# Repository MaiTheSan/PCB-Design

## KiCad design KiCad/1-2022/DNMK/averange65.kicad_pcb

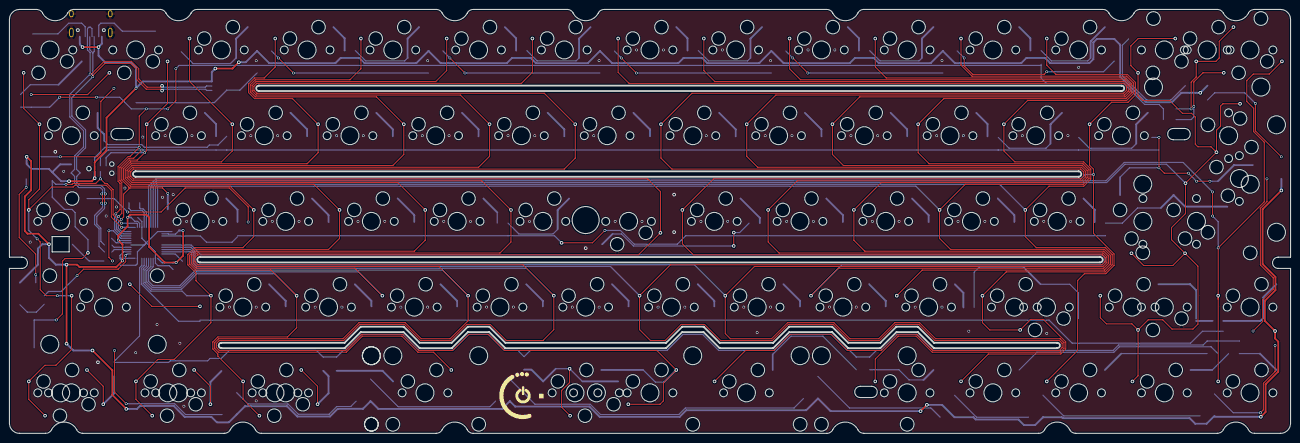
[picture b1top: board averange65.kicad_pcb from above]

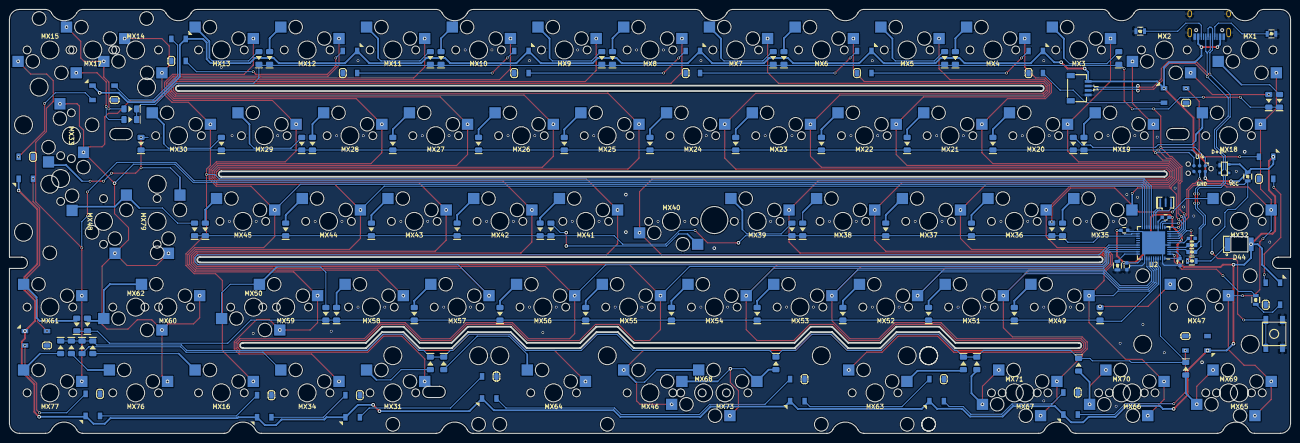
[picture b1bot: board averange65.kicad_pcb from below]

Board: 2 copper layers, 284.7 x 94.2 mm, 183 parts (107 on the bottom side), 122 nets.

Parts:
C1: 10uF; C_0603
C4, C5, C7: 0.1uF; C_0603
C6: 1uF; C_0603
D1, D2, D3, D4, D5, D6, D7, D8, D9, D10, D11, D12, D13, D14, D15, D16, D17, D18, D19, D20, D21, D22, D23, D24, D25, D26, D27, D28, D29, D30, D31, D33, D34, D35, D36, D37, D38, D39, D40, D41, D42, D43, D45, D46, D48, D49, D50, D51, D52, D53, D54, D55, D56, D57, D58, D59, D61, D62, D63, D64, D65, D66, D70, D71, D72, D73: D; DIODE_1206_SawnsProjects
D44: LED; LED-6028
J1: Conn_01x04_Female; JST-SR-4
MX1, MX2, MX3, MX4, MX5, MX6, MX7, MX8, MX9, MX10, MX11, MX12, MX13, MX14, MX15, MX16, MX19, MX20, MX21, MX22, MX23, MX24, MX25, MX26, MX27, MX28, MX29, MX30, MX31, MX34, MX35, MX36, MX37, MX38, MX39, MX40, MX41, MX42, MX43, MX44, MX45, MX49, MX51, MX52, MX53, MX54, MX55, MX56, MX57, MX58, MX59, MX61, MX62, MX70, MX76, MX77, MX79: 1U; MXOnly-1U-Hotswap
MX17: 2U; MXOnly-2U-Hotswap
MX18, MX33, MX69, MX71: 1.5U; MXOnly-1.5U-Hotswap
MX32: 1.75U; MXOnly-1.25U-Hotswap
MX46: 7U; MXOnly-7U-Hotswap-ReversedStabilizers
MX47: 2.25U; MXOnly-2.25U-Hotswap
MX48: 2.25U; MXOnly-2.25U-Hotswap-ReversedStabilizers-L
MX50, MX60: 1.75U; MXOnly-1.75U-Hotswap
MX63: 2.25U; MXOnly-2.25U-Hotswap-ReversedStabilizers
MX64: 2.75U; MXOnly-2.75U-Hotswap-ReversedStabilizers
MX65, MX66, MX67, MX73: 1.25U; MXOnly-1.25U-Hotswap
MX68: 6.25U; MXOnly-6.25U-Hotswap
MX78: ISO; MXOnly-ISO-ROTATED-Hotswap-R
R1, R2: 5.1k; R_0805
R3, R4: 22; R_0603
R5: 10k; R_0805
R6: 1k; R_0805
R7, R8: 300R; R_0805
RGB1, RGB2, RGB3, RGB4, RGB5, RGB6, RGB7, RGB8, RGB9, RGB10, RGB11, RGB12, RGB13, RGB14, RGB15, RGB16, RGB17, RGB18, RGB19, RGB20: WS2812B; LED_WS2812B_PLCC4_5.0x5.0mm_P3.2mm
SW1: SW_Push; SKQG-1155865
U1: PRTR5V0U2X; SOT143B
U2: ATmega32U4-MU; QFN-44-1EP_7x7mm_P0.5mm_EP5.15x5.15mm
U4: STF202-22T1G; Tag-Connect_TC2030-IDC-NL_2x03_P1.27mm_Vertical
USB1: HRO-TYPE-C-31-M-12; HRO-TYPE-C-31-M-12-Assembly
Y1: Crystal_GND2; Resonator_SMD_muRata_CSTxExxV-3Pin_3.0x1.1mm

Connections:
+5V: C1.2, C4.2, C5.2, C7.2, D44.2, J1.1, R5.1, RGB1.1, RGB2.1, RGB3.1, RGB4.1, RGB5.1, RGB6.1, RGB7.1, RGB8.1, RGB9.1, RGB10.1, RGB11.1, RGB12.1, RGB13.1, RGB14.1, RGB15.1, RGB16.1, RGB17.1, RGB18.1, RGB19.1, RGB20.1, U1.4, U2.2, U2.7, U2.14, U2.24, U2.34, U2.44, U4.2, USB1.2, USB1.11
A+: J1.3, R4.2, U1.2, USB1.6, USB1.8
A-: J1.2, R3.2, U1.3, USB1.5, USB1.7
CapLK: R8.2, U2.8
Col0: MX1.2, MX18.1, MX32.1, MX47.1, MX65.1, MX69.2, U2.12
Col1: MX2.1, MX19.1, MX35.1, U2.11, U4.5
Col2: MX3.1, MX20.1, MX36.1, MX49.1, MX66.1, MX70.2, U2.39
Col3: MX4.1, MX21.1, MX37.1, MX51.1, MX67.1, MX71.2, U2.38
Col4: MX5.1, MX22.1, MX38.1, MX52.1, U2.37
Col5: MX6.1, MX23.1, MX39.1, MX53.1, MX63.2, U2.36
Col6: MX7.1, MX24.1, MX40.1, MX46.2, MX54.1, MX68.1, MX73.2, U2.32
Col7: MX8.1, MX25.1, MX41.1, MX55.1, MX64.1, U2.31
Col8: MX9.1, MX26.1, MX31.1, MX42.1, MX56.1, U2.30
Col9: MX10.1, MX27.1, MX43.1, MX57.1, U2.29
Col10: MX11.1, MX28.1, MX44.1, MX58.1, U2.22
Col11: MX12.1, MX29.1, MX34.1, MX45.1, MX50.2, MX59.1, U2.21
Col12: MX13.1, MX16.1, MX30.1, U2.18
Col13: MX14.2, MX17.1, MX33.1, MX48.1, MX60.1, MX62.2, MX76.1, MX78.2, MX79.1, U2.20
Col14: MX15.1, MX61.1, MX77.1, U2.19
D+: R4.1, U2.4
D-: R3.1, U2.3
GND: C1.1, C4.1, C5.1, C6.2, C7.1, J1.4, R1.1, R2.1, R6.1, RGB1.3, RGB2.3, RGB3.3, RGB4.3, RGB5.3, RGB6.3, RGB7.3, RGB8.3, RGB9.3, RGB10.3, RGB11.3, RGB12.3, RGB13.3, RGB14.3, RGB15.3, RGB16.3, RGB17.3, RGB18.3, RGB19.3, RGB20.3, SW1.1, U1.1, U2.5, U2.15, U2.23, U2.35, U2.43, U2.45, U4.6, USB1.1, USB1.12, USB1.13, Y1.2
MOSI: D17.1, D18.1, D19.1, D20.1, D21.1, D22.1, D23.1, D24.1, D25.1, D26.1, D27.1, D28.1, D29.1, D31.1, U2.10, U4.3
unnamed: C6.1, U2.6
unnamed: D1.2, MX1.1
unnamed: D2.2, MX2.2
unnamed: D3.2, MX3.2
unnamed: D4.2, MX4.2
unnamed: D5.2, MX5.2
unnamed: D6.2, MX6.2
unnamed: D7.2, MX7.2
unnamed: D8.2, MX8.2
unnamed: D9.2, MX9.2
unnamed: D10.2, MX10.2
unnamed: D11.2, MX11.2
unnamed: D12.2, MX12.2
unnamed: D13.2, MX13.2
unnamed: D14.2, MX14.1, MX17.2
unnamed: D15.2, MX15.2
unnamed: D16.2, MX16.2
unnamed: D17.2, MX18.2
unnamed: D18.2, MX19.2
unnamed: D19.2, MX20.2
unnamed: D20.2, MX21.2
unnamed: D21.2, MX22.2
unnamed: D22.2, MX23.2
unnamed: D23.2, MX24.2
unnamed: D24.2, MX25.2
unnamed: D25.2, MX26.2
unnamed: D26.2, MX27.2
unnamed: D27.2, MX28.2
unnamed: D28.2, MX29.2
unnamed: D29.2, MX30.2
unnamed: D30.2, MX32.2
unnamed: D31.2, MX33.2, MX79.2
unnamed: D33.2, MX35.2
unnamed: D34.2, MX36.2
unnamed: D35.2, MX37.2
unnamed: D36.2, MX38.2
unnamed: D37.2, MX39.2
unnamed: D38.2, MX40.2
unnamed: D39.2, MX41.2
unnamed: D40.2, MX42.2
unnamed: D41.2, MX43.2
unnamed: D42.2, MX44.2
unnamed: D43.2, MX45.2
unnamed: D44.1, R8.1
unnamed: D45.2, MX48.2, MX78.1
unnamed: D46.2, MX47.2
unnamed: D48.2, MX49.2
unnamed: D49.2, MX51.2
unnamed: D50.2, MX52.2
unnamed: D51.2, MX53.2
unnamed: D52.2, MX54.2
unnamed: D53.2, MX55.2
unnamed: D54.2, MX56.2
unnamed: D55.2, MX57.2
unnamed: D56.2, MX58.2
unnamed: D57.2, MX50.1, MX59.2
unnamed: D58.2, MX60.2, MX62.1
unnamed: D59.2, MX61.2
unnamed: D61.2, MX65.2, MX69.1
unnamed: D62.2, MX66.2, MX70.1
unnamed: D63.2, MX67.2, MX71.1
unnamed: D64.2, MX63.1
unnamed: D65.2, MX46.1, MX68.2, MX73.1
unnamed: D66.2, MX64.2
unnamed: D70.2, MX31.2
unnamed: D71.2, MX34.2
unnamed: D72.2, MX76.2
unnamed: D73.2, MX77.2
unnamed: R1.2, USB1.4
unnamed: R2.2, USB1.10
unnamed: R6.2, U2.33
unnamed: R7.2, U2.1
unnamed: RGB1.2, RGB2.4
unnamed: RGB1.4, RGB11.2
unnamed: RGB2.2, RGB3.4
unnamed: RGB3.2, RGB4.4
unnamed: RGB4.2, RGB5.4
unnamed: RGB5.2, RGB6.4
unnamed: RGB6.2, RGB7.4
unnamed: RGB7.2, RGB8.4
unnamed: RGB8.2, RGB9.4
unnamed: RGB10.2, RGB20.4
unnamed: RGB9.2, RGB10.4
unnamed: RGB11.4, RGB12.2
unnamed: RGB13.4, RGB14.2
unnamed: RGB14.4, RGB15.2
unnamed: RGB15.4, RGB16.2
unnamed: RGB16.4, RGB17.2
unnamed: RGB17.4, RGB18.2
unnamed: RGB18.4, RGB19.2
unnamed: RGB19.4, RGB20.2
unnamed: U2.16, Y1.3
unnamed: U2.17, Y1.1
RGBLED: R7.1, RGB12.4
RST: R5.2, SW1.2, U2.13, U4.4
Row0: D1.1, D2.1, D3.1, D4.1, D5.1, D6.1, D7.1, D8.1, D9.1, D10.1, D11.1, D12.1, D13.1, D14.1, D15.1, U2.9, U4.1
Row2: D30.1, D33.1, D34.1, D35.1, D36.1, D37.1, D38.1, D39.1, D40.1, D41.1, D42.1, D43.1, D45.1, U2.25
Row3: D46.1, D48.1, D49.1, D50.1, D51.1, D52.1, D53.1, D54.1, D55.1, D56.1, D57.1, D58.1, D59.1, U2.40
Row4: D16.1, D61.1, D62.1, D63.1, D64.1, D65.1, D66.1, D70.1, D71.1, D72.1, D73.1, U2.41

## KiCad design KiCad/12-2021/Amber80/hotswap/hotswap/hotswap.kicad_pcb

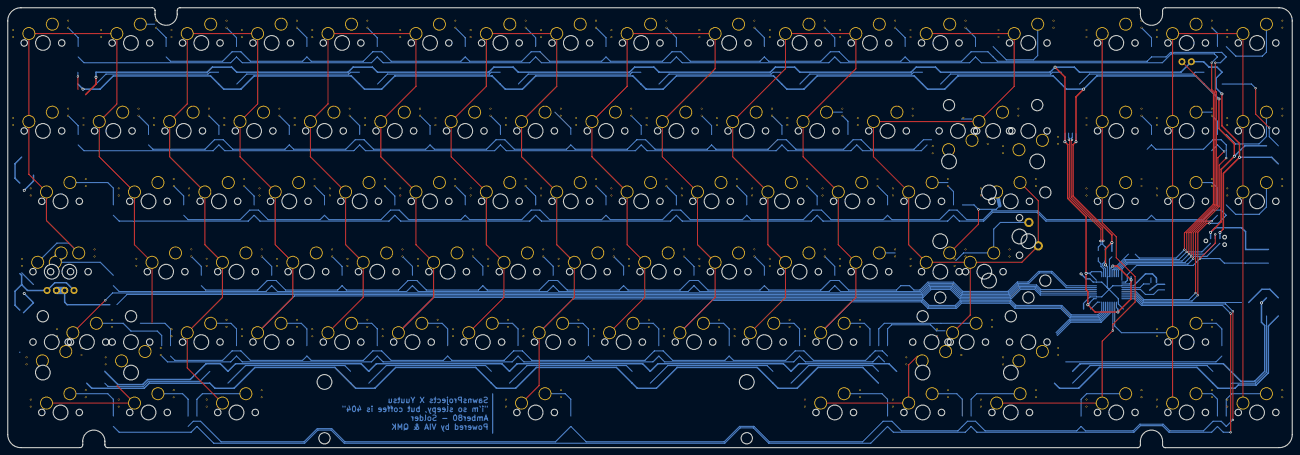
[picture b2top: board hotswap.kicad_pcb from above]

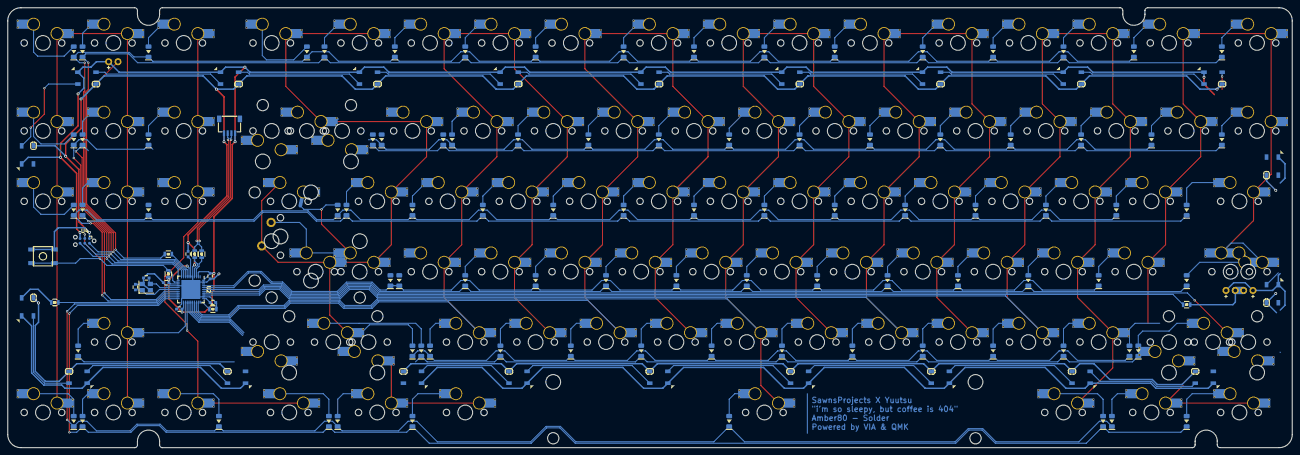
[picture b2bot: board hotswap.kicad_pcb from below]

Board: 2 copper layers, 347.7 x 119.1 mm, 230 parts (131 on the bottom side), 149 nets.

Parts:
C1: 10uF; C_0603
C2, C3: 22pF; C_0603
C4, C5, C7: 0.1uF; C_0603
C6: 1uF; C_0603
D1, D2, D3, D4, D5, D6, D7, D8, D9, D10, D11, D12, D13, D14, D15, D16, D17, D18, D19, D20, D21, D22, D23, D25, D26, D27, D28, D29, D31, D32, D33, D34, D35, D37, D38, D39, D40, D41, D43, D44, D45, D46, D47, D48, D49, D50, D51, D52, D53, D55, D56, D57, D58, D59, D61, D62, D63, D64, D65, D67, D68, D69, D70, D71, D73, D74, D75, D77, D78, D79, D80, D81, D82, D83, D84, D86, D87, D90, D91, D92, D93, D96, D97, D98, D101, D102, D103, D104, D105, D108: D; DIODE_1206_SawnsProjects
D24, D30, D36, D42, D54, D60, D66, D72, D76, D85, D88, D89, D94, D95, D99, D100, D106, D107, D109, D110, D111, D112: WS2812B; LED_WS2812B_PLCC4_5.0x5.0mm_P3.2mm
D113, D115: LED; MXOnly-LEDONLY-FLIPPED
D114: LED; MXOnly-LEDONLY
J1: Conn_01x04_Female; JST-SR-4
MX1, MX2, MX3, MX4, MX5, MX6, MX7, MX8, MX9, MX10, MX11, MX12, MX13, MX14, MX16, MX17, MX22, MX23, MX24, MX25, MX26, MX27, MX28, MX29, MX30, MX32, MX33, MX34, MX35, MX37, MX38, MX39, MX40, MX41, MX42, MX43, MX44, MX45, MX47, MX48, MX49, MX50, MX52, MX53, MX54, MX55, MX57, MX58, MX59, MX60, MX62, MX63, MX64, MX65, MX67, MX68, MX69, MX70, MX72, MX73, MX74, MX75, MX77, MX78, MX79, MX82, MX85, MX87, MX88, MX92, MX93, MX96, MX97, MX98, MX101, MX102, MX103, MX104, MX105, MX108: 1U; MXOnly-1U-Hotswap-Sawns
MX15, MX18, MX21, MX31, MX36, MX46: 1.5U; MXOnly-1.5U-Hotswap-Sawns
MX19, MX80: 1.75U; MXOnly-1.75U-Hotswap-Sawns
MX20, MX71: 1.25U; MXOnly-1.25U-Hotswap-Sawns
MX51: 2U; MXOnly-2U-Hotswap-Sawns
MX56: 7U; MXOnly-7U-Hotswap-ReversedStabilizers-Sawns
MX61: 2.75U; MXOnly-2.75U-Hotswap-Sawns
MX66: 2.25U; MXOnly-2.25U-Hotswap-Sawns
MX76: ISO; MXOnly-ISO-ROTATED-ReversedStabilizers-NoLED
MX84: 2.25U; MXOnly-2.75U-Hotswap-ReversedStabilizers-Sawns
R3, R4: 22; R_0805
R5: 10k; R_0805
R6: 1k; R_0805
R7, R8, R9: 300R; R_0805
SW1: SW_Push; SKQG-1155865-fix
U2: ATmega32U4-MU; QFN-44-1EP_7x7mm_P0.5mm_EP5.15x5.15mm
U4: STF202-22T1G; Tag-Connect_TC2030-IDC-NL_2x03_P1.27mm_Vertical
Y1: 16Mhz; Crystal_SMD_3225-4Pin_3.2x2.5mm

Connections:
+5V: C1.2, C4.2, C5.2, C7.2, D24.1, D30.1, D36.1, D42.1, D54.1, D60.1, D66.1, D72.1, D76.1, D85.1, D88.1, D89.1, D94.1, D95.1, D99.1, D100.1, D106.1, D107.1, D109.1, D110.1, D111.1, D112.1, D113.2, D114.2, D115.2, J1.1, R5.1, U2.2, U2.7, U2.14, U2.24, U2.34, U2.44, U4.5
C0: MX1.1, MX2.1, MX17.1, MX18.1, MX19.2, MX20.1, MX21.1, MX22.1, MX23.1, MX24.1, MX25.1, MX26.1, MX66.1, MX71.1, U2.39
C1: MX3.1, MX4.1, MX27.1, MX28.1, MX29.1, MX30.1, MX31.1, MX32.1, MX33.1, MX34.1, MX35.1, U2.37
C2: MX5.1, MX6.1, MX37.1, MX38.1, MX39.1, MX40.1, MX42.1, MX43.1, MX44.1, MX45.1, U2.36
C3: MX7.1, MX8.1, MX47.1, MX48.1, MX49.1, MX50.1, MX52.1, MX53.1, MX54.1, MX55.1, MX56.1, U2.32
C4: MX9.1, MX10.1, MX57.1, MX58.1, MX59.1, MX60.1, MX62.1, MX63.1, MX64.1, MX65.1, U2.31
C5: MX11.1, MX12.1, MX67.1, MX68.1, MX69.1, MX70.1, MX72.1, MX73.1, MX74.1, MX75.1, U2.30
C6: MX13.1, MX14.1, MX15.2, MX36.1, MX41.1, MX51.1, MX61.1, MX76.2, MX77.1, MX78.1, MX79.1, MX80.1, MX82.1, MX84.1, MX85.1, U2.29
C7: MX16.1, MX46.1, MX87.1, MX88.1, MX92.1, MX96.1, U2.26
C8: MX93.1, MX97.1, MX98.1, MX101.1, MX102.1, MX103.1, MX104.1, MX105.1, MX108.1, U2.25
D+: R3.1, U2.4
D-: R4.1, U2.3
DG+: J1.3, R3.2
DG-: J1.2, R4.2
GND: C1.1, C2.2, C3.2, C4.1, C5.1, C6.2, C7.1, D24.3, D30.3, D36.3, D42.3, D54.3, D60.3, D66.3, D72.3, D76.3, D85.3, D88.3, D89.3, D94.3, D95.3, D99.3, D100.3, D106.3, D107.3, D109.3, D110.3, D111.3, D112.3, J1.4, R6.1, SW1.1, U2.5, U2.15, U2.23, U2.35, U2.43, U2.45, U4.1, Y1.2, Y1.4
MISO: D2.1, D14.1, D26.1, D38.1, D50.1, D62.1, D74.1, D86.1, D98.1, U2.11, U4.6
MOSI: D7.1, D19.1, D31.1, D43.1, D55.1, D67.1, D79.1, D91.1, D103.1, U2.10, U4.4
unnamed: C2.1, U2.17, Y1.1
unnamed: C3.1, U2.16, Y1.3
unnamed: C6.1, U2.6
unnamed: D1.2, MX1.2
unnamed: D2.2, MX17.2
unnamed: D3.2, MX18.2
unnamed: D4.2, MX19.1, MX71.2
unnamed: D5.2, MX20.2, MX66.2
unnamed: D6.2, MX21.2
unnamed: D7.2, MX2.2
unnamed: D8.2, MX22.2
unnamed: D9.2, MX23.2
unnamed: D10.2, MX24.2
unnamed: D11.2, MX25.2
unnamed: D12.2, MX26.2
unnamed: D13.2, MX3.2
unnamed: D14.2, MX27.2
unnamed: D15.2, MX28.2
unnamed: D16.2, MX29.2
unnamed: D17.2, MX30.2
unnamed: D18.2, MX31.2
unnamed: D19.2, MX4.2
unnamed: D20.2, MX32.2
unnamed: D21.2, MX33.2
unnamed: D22.2, MX34.2
unnamed: D23.2, MX35.2
unnamed: D24.4, D30.2
unnamed: D25.2, MX5.2
unnamed: D26.2, MX37.2
unnamed: D27.2, MX38.2
unnamed: D28.2, MX39.2
unnamed: D29.2, MX40.2
unnamed: D30.4, D36.2
unnamed: D31.2, MX6.2
unnamed: D32.2, MX42.2
unnamed: D33.2, MX43.2
unnamed: D34.2, MX44.2
unnamed: D35.2, MX45.2
unnamed: D36.4, D42.2
unnamed: D37.2, MX7.2
unnamed: D38.2, MX47.2
unnamed: D39.2, MX48.2
unnamed: D40.2, MX49.2
unnamed: D41.2, MX50.2
unnamed: D42.4, D54.2
unnamed: D43.2, MX8.2
unnamed: D44.2, MX52.2
unnamed: D45.2, MX53.2
unnamed: D46.2, MX54.2
unnamed: D47.2, MX55.2
unnamed: D48.2, MX56.2
unnamed: D49.2, MX9.2
unnamed: D50.2, MX57.2
unnamed: D51.2, MX58.2
unnamed: D52.2, MX59.2
unnamed: D53.2, MX60.2
unnamed: D54.4, D60.2
unnamed: D55.2, MX10.2
unnamed: D56.2, MX62.2
unnamed: D57.2, MX63.2
unnamed: D58.2, MX64.2
unnamed: D59.2, MX65.2
unnamed: D60.4, D66.2
unnamed: D61.2, MX11.2
unnamed: D62.2, MX67.2
unnamed: D63.2, MX68.2
unnamed: D64.2, MX69.2
unnamed: D65.2, MX70.2
unnamed: D66.4, D72.2
unnamed: D67.2, MX12.2
unnamed: D68.2, MX72.2
unnamed: D69.2, MX73.2
unnamed: D70.2, MX74.2
unnamed: D71.2, MX75.2
unnamed: D72.4, D76.2
unnamed: D73.2, MX13.2
unnamed: D74.2, MX77.2
unnamed: D75.2, MX78.2
unnamed: D76.4, D85.2
unnamed: D77.2, MX61.2, MX80.2
unnamed: D78.2, MX36.2
unnamed: D79.2, MX14.2
unnamed: D80.2, MX51.2, MX82.2
unnamed: D81.2, MX15.1, MX79.2
unnamed: D82.2, MX76.1, MX84.2
unnamed: D83.2, MX85.2
unnamed: D84.2, MX41.2
unnamed: D85.4, D88.2
unnamed: D86.2, MX87.2
unnamed: D87.2, MX93.2
unnamed: D88.4, D89.2
unnamed: D89.4, D94.2
unnamed: D90.2, MX46.2
unnamed: D91.2, MX16.2
unnamed: D92.2, MX92.2
unnamed: D93.2, MX88.2
unnamed: D95.2, D99.4
unnamed: D95.4, R7.1
unnamed: D96.2, MX96.2
unnamed: D97.2, MX97.2
unnamed: D98.2, MX98.2
unnamed: D100.2, D106.4
unnamed: D99.2, D100.4
unnamed: D101.2, MX101.2
unnamed: D102.2, MX102.2
unnamed: D103.2, MX103.2
unnamed: D104.2, MX104.2
unnamed: D105.2, MX105.2
unnamed: D106.2, D107.4
unnamed: D107.2, D109.4
unnamed: D108.2, MX108.2
unnamed: D109.2, D110.4
unnamed: D110.2, D111.4
unnamed: D111.2, D112.4
unnamed: D94.4, D112.2
unnamed: D113.1, R8.1
unnamed: D114.1, D115.1, R9.1
unnamed: R6.2, U2.33
R0: D1.1, D13.1, D25.1, D37.1, D49.1, D61.1, D73.1, D97.1, U2.9, U4.2
R3: D8.1, D20.1, D32.1, D44.1, D56.1, D68.1, D80.1, D92.1, D104.1, U2.12
R4: D3.1, D15.1, D27.1, D39.1, D51.1, D63.1, D75.1, D87.1, U2.18
R5: D9.1, D21.1, D33.1, D45.1, D57.1, D69.1, D81.1, D93.1, D105.1, U2.19
R6: D4.1, D16.1, D28.1, D40.1, D52.1, D64.1, U2.40
R7: D10.1, D22.1, D34.1, D46.1, D58.1, D70.1, D82.1, U2.41
R8: D5.1, D17.1, D29.1, D41.1, D53.1, D65.1, D77.1, D101.1, U2.27
R9: D11.1, D23.1, D35.1, D47.1, D59.1, D71.1, D83.1, U2.28
R10: D6.1, D18.1, D78.1, D90.1, D102.1, U2.22
R11: D12.1, D48.1, D84.1, D96.1, D108.1, U2.21
RGB: R7.2, U2.20
RST: R5.2, SW1.2, U2.13, U4.3
indicator1: R8.2, U2.8
indicator2: R9.2, U2.38

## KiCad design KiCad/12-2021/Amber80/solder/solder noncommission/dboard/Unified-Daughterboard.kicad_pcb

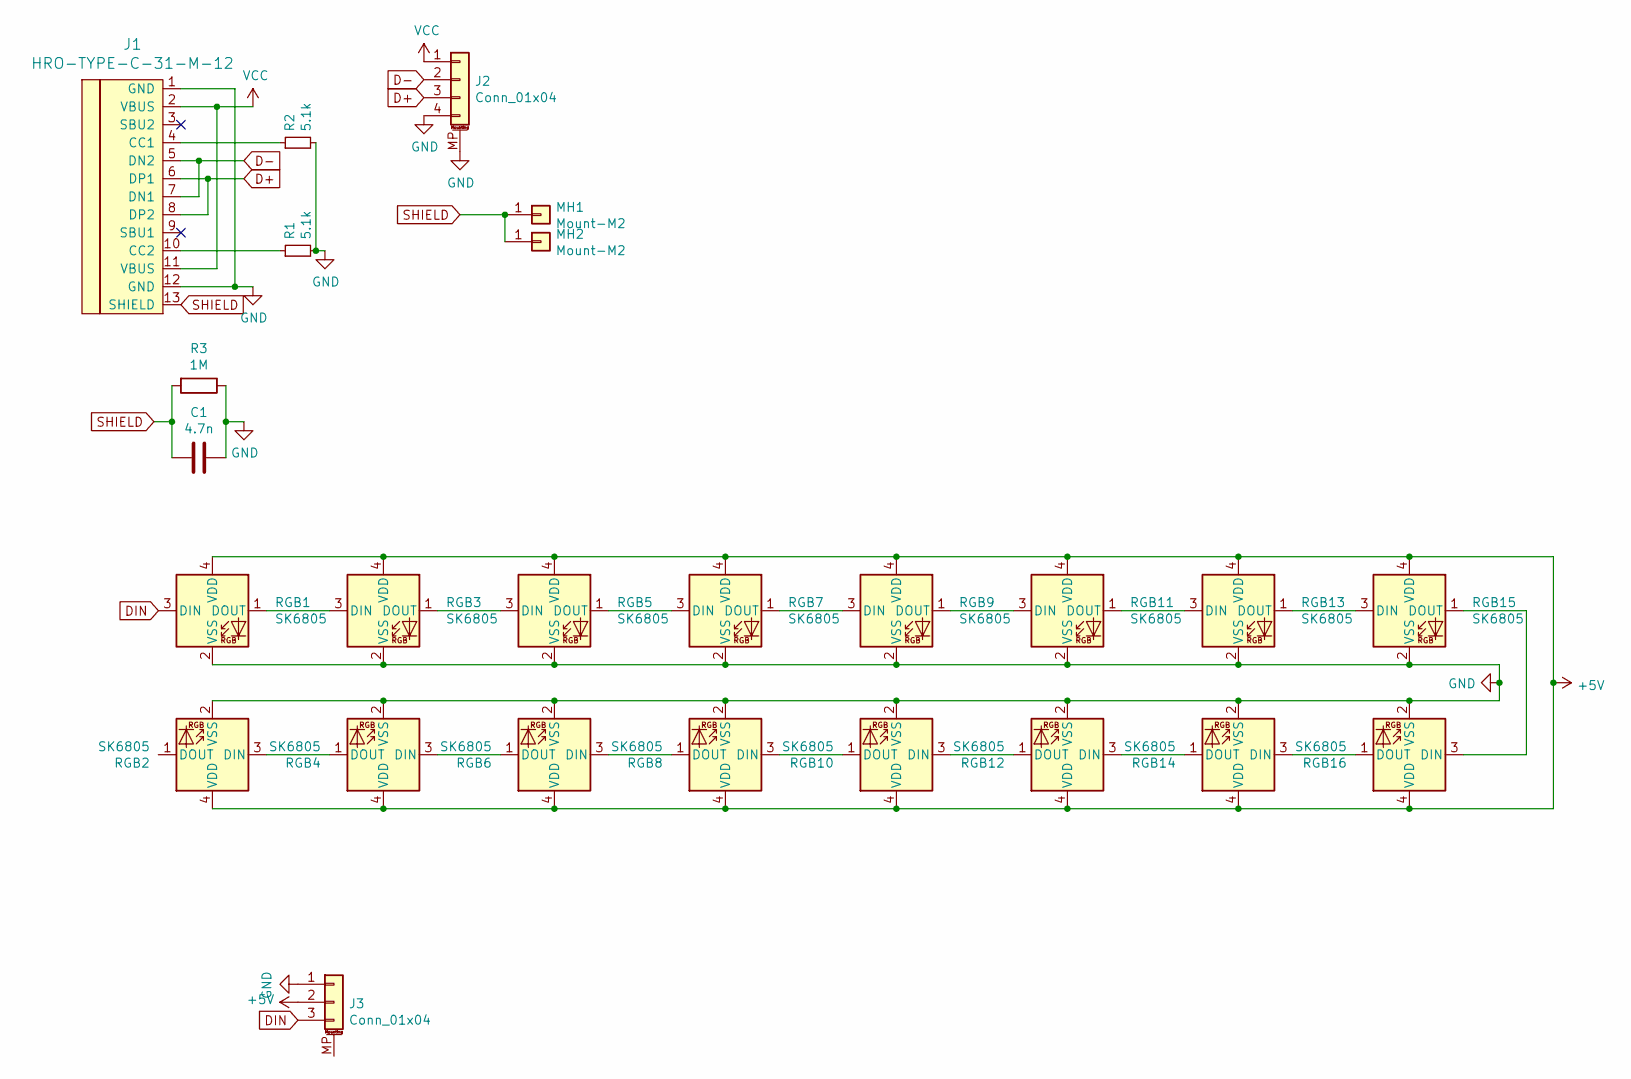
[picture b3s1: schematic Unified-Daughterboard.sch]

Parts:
C1: 4.7n; C_0603_1608Metric; LCSC C53987
J1: HRO-TYPE-C-31-M-12; HRO-TYPE-C-31-M-12-jlc; LCSC C165948
J2: Conn_01x04; JST-SR-4
J3: Conn_01x04; PinHeader_1x03_P2.54mm_Vertical
MH1, MH2: Mount-M2; MountingHole_3.2mm_M3_Pad_Via
R1, R2: 5.1k; R_0603_1608Metric; LCSC C23186
R3: 1M; R_0805_2012Metric; LCSC C17514
RGB1, RGB2, RGB3, RGB4, RGB5, RGB6, RGB7, RGB8, RGB9, RGB10, RGB11, RGB12, RGB13, RGB14, RGB15, RGB16: SK6805; LED_SK6805_PLCC4_2.4x2.7mm_P1.3mm

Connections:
+5V: J3.2, RGB1.4 (VDD), RGB2.4 (VDD), RGB3.4 (VDD), RGB4.4 (VDD), RGB5.4 (VDD), RGB6.4 (VDD), RGB7.4 (VDD), RGB8.4 (VDD), RGB9.4 (VDD), RGB10.4 (VDD), RGB11.4 (VDD), RGB12.4 (VDD), RGB13.4 (VDD), RGB14.4 (VDD), RGB15.4 (VDD), RGB16.4 (VDD)
D+: J1.6 (DP1), J1.8 (DP2), J2.3
D-: J1.5 (DN2), J1.7 (DN1), J2.2
DIN: J3.3, RGB1.3 (DIN)
GND: C1.1, J1.1 (GND), J1.12 (GND), J2.4, J2.MP (MountPin), J3.1, R1.2, R2.2, R3.1, RGB1.2 (VSS), RGB2.2 (VSS), RGB3.2 (VSS), RGB4.2 (VSS), RGB5.2 (VSS), RGB6.2 (VSS), RGB7.2 (VSS), RGB8.2 (VSS), RGB9.2 (VSS), RGB10.2 (VSS), RGB11.2 (VSS), RGB12.2 (VSS), RGB13.2 (VSS), RGB14.2 (VSS), RGB15.2 (VSS), RGB16.2 (VSS)
unnamed: J1.4 (CC1), R2.1
unnamed: J1.10 (CC2), R1.1
unnamed: RGB1.1 (DOUT), RGB3.3 (DIN)
unnamed: RGB2.3 (DIN), RGB4.1 (DOUT)
unnamed: RGB3.1 (DOUT), RGB5.3 (DIN)
unnamed: RGB4.3 (DIN), RGB6.1 (DOUT)
unnamed: RGB5.1 (DOUT), RGB7.3 (DIN)
unnamed: RGB6.3 (DIN), RGB8.1 (DOUT)
unnamed: RGB7.1 (DOUT), RGB9.3 (DIN)
unnamed: RGB8.3 (DIN), RGB10.1 (DOUT)
unnamed: RGB10.3 (DIN), RGB12.1 (DOUT)
unnamed: RGB11.1 (DOUT), RGB13.3 (DIN)
unnamed: RGB9.1 (DOUT), RGB11.3 (DIN)
unnamed: RGB12.3 (DIN), RGB14.1 (DOUT)
unnamed: RGB13.1 (DOUT), RGB15.3 (DIN)
unnamed: RGB14.3 (DIN), RGB16.1 (DOUT)
unnamed: RGB15.1 (DOUT), RGB16.3 (DIN)
SHIELD: C1.2, J1.13 (SHIELD), MH1.1, MH2.1, R3.2
VCC: J1.2 (VBUS), J1.11 (VBUS), J2.1

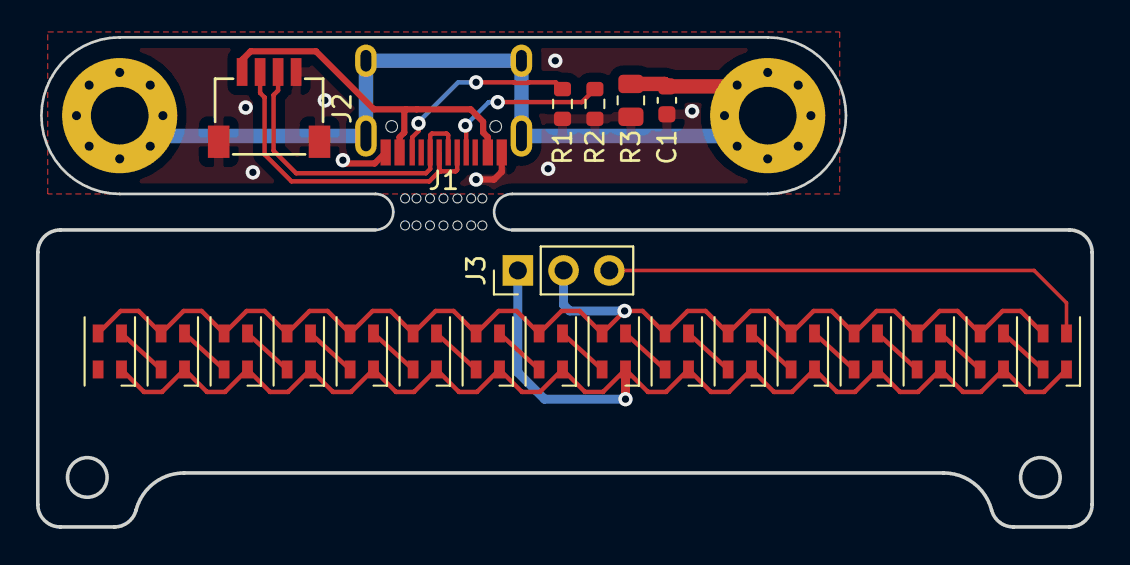
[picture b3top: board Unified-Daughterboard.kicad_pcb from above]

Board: 2 copper layers, 58.6 x 27.2 mm, 26 parts (0 on the bottom side), 24 nets.

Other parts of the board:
mouse-bite-3mm-slot: VAL**; mouse-bite-7mm-slot

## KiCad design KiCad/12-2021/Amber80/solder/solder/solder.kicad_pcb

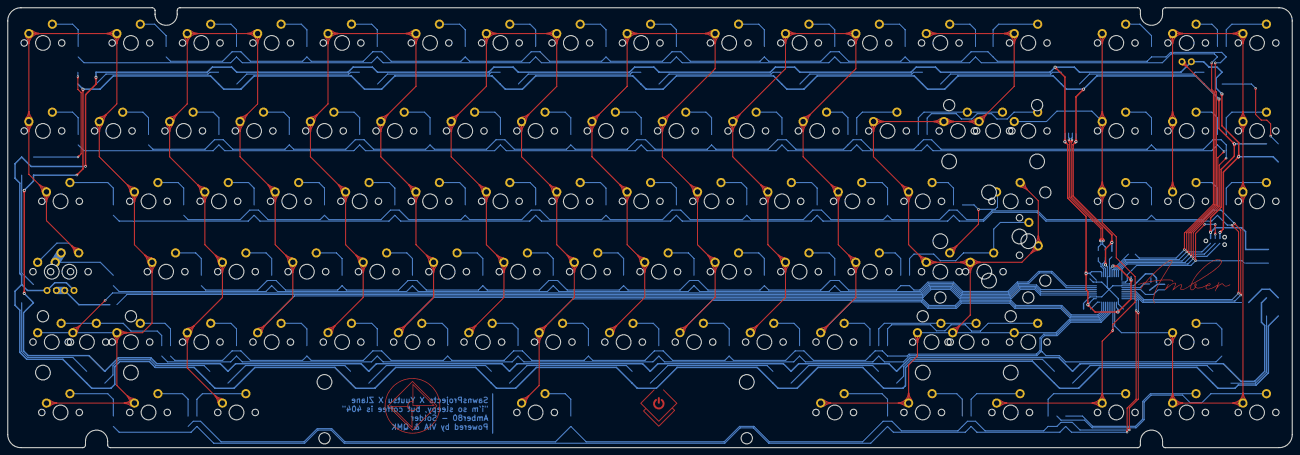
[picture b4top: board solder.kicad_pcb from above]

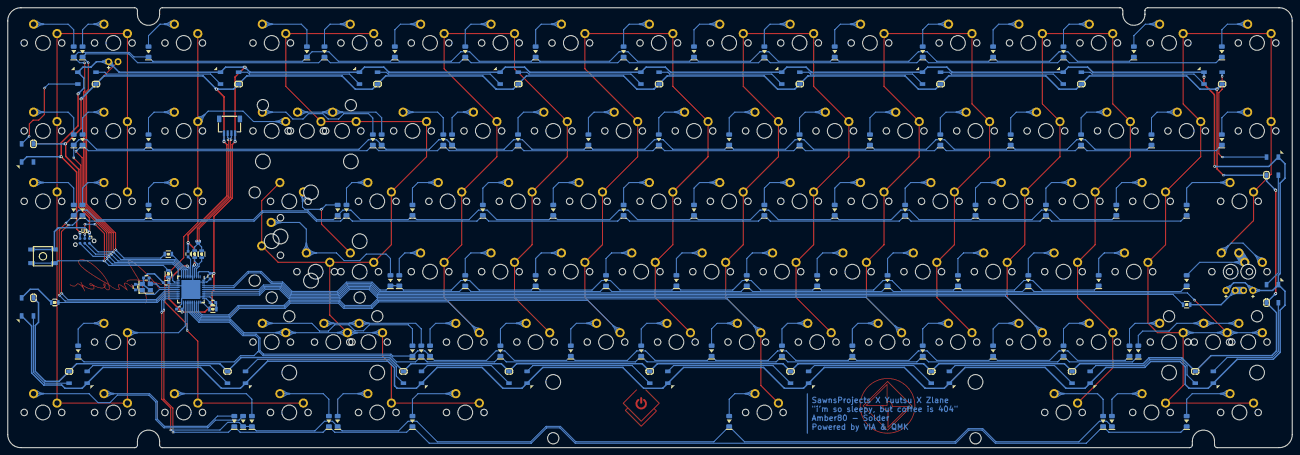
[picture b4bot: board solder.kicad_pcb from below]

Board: 2 copper layers, 347.7 x 119.1 mm, 230 parts (131 on the bottom side), 149 nets.

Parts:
C1: 10uF; C_0603
C2, C3: 22pF; C_0603
C4, C5, C7: 0.1uF; C_0603
C6: 1uF; C_0603
D1, D2, D3, D4, D5, D6, D7, D8, D9, D10, D11, D12, D13, D14, D15, D16, D17, D18, D19, D20, D21, D22, D23, D24, D25, D26, D27, D28, D29, D30, D31, D32, D33, D34, D35, D36, D37, D38, D39, D40, D41, D42, D43, D44, D45, D46, D47, D48, D49, D50, D51, D52, D53, D54, D55, D56, D57, D58, D59, D60, D61, D62, D63, D64, D65, D66, D67, D68, D69, D70, D71, D72, D73, D74, D75, D76, D77, D78, D79, D80, D81, D82, D83, D84, D85, D86, D87, D88, D89, D90: D; DIODE_1206_SawnsProjects
J1: Conn_01x04_Female; JST-SR-4
LED1, LED3: LED; MXOnly-LEDONLY-FLIPPED
LED2: LED; MXOnly-LEDONLY
MX1, MX2, MX9, MX10, MX11, MX12, MX13, MX14, MX15, MX16, MX17, MX18, MX19, MX21, MX22, MX23, MX24, MX25, MX26, MX27, MX28, MX29, MX30, MX31, MX32, MX33, MX34, MX35, MX36, MX37, MX38, MX39, MX40, MX41, MX42, MX43, MX44, MX45, MX47, MX48, MX49, MX50, MX51, MX52, MX53, MX54, MX55, MX56, MX57, MX58, MX59, MX60, MX61, MX62, MX63, MX64, MX65, MX66, MX67, MX68, MX69, MX73, MX74, MX76, MX78, MX79, MX82, MX84, MX85, MX86, MX87, MX88, MX89, MX90, MX91, MX92, MX93, MX94, MX95, MX96: 1U; MXOnly-1U-NoLED
MX3, MX7, MX20, MX72, MX80, MX83: 1.5U; MXOnly-1.5U-NoLED
MX4, MX5: 1.25U; MXOnly-1.25U-NoLED
MX6: 2.25U; MXOnly-2.25U-NoLED
MX8, MX70: 1.75U; MXOnly-1.75U-NoLED
MX46: 7U; MXOnly-7U-ReversedStabilizers-NoLED
MX71: 2.75U; MXOnly-2.75U-NoLED
MX75: 2U; MXOnly-2U-NoLED
MX77: 2.25U; MXOnly-2.25U-ReversedStabilizers-NoLED
MX81: ISO; MXOnly-ISO-ROTATED-ReversedStabilizers-NoLED
R1, R2, R3: 300R; R_0805
R4, R5: 22; R_0805
R6: 10k; R_0805
R7: 1k; R_0805
RGB1, RGB2, RGB3, RGB4, RGB5, RGB6, RGB7, RGB8, RGB9, RGB10, RGB11, RGB12, RGB13, RGB14, RGB15, RGB16, RGB17, RGB18, RGB19, RGB20, RGB21, RGB22: WS2812B; LED_WS2812B_PLCC4_5.0x5.0mm_P3.2mm
SW1: SW_Push; SKQG-1155865-fix
U1: STF202-22T1G; Tag-Connect_TC2030-IDC-NL_2x03_P1.27mm_Vertical
U2: ATmega32U4-MU; QFN-44-1EP_7x7mm_P0.5mm_EP5.15x5.15mm
Y1: 16Mhz; Crystal_SMD_3225-4Pin_3.2x2.5mm

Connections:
+5V: C1.2, C4.2, C5.2, C7.2, J1.1, LED1.2, LED2.2, LED3.2, R6.1, RGB1.1, RGB2.1, RGB3.1, RGB4.1, RGB5.1, RGB6.1, RGB7.1, RGB8.1, RGB9.1, RGB10.1, RGB11.1, RGB12.1, RGB13.1, RGB14.1, RGB15.1, RGB16.1, RGB17.1, RGB18.1, RGB19.1, RGB20.1, RGB21.1, RGB22.1, U1.5, U2.2, U2.7, U2.14, U2.24, U2.34, U2.44
C0: MX1.1, MX2.1, MX3.1, MX4.1, MX5.1, MX6.1, MX7.1, MX8.2, MX9.1, MX10.1, MX11.1, MX12.1, MX13.1, MX14.1, U2.39
C1: MX15.1, MX16.1, MX17.1, MX18.1, MX19.1, MX20.1, MX21.1, MX22.1, MX23.1, MX24.1, MX25.1, U2.37
C2: MX26.1, MX27.1, MX28.1, MX29.1, MX30.1, MX31.1, MX32.1, MX33.1, MX34.1, MX35.1, U2.36
C3: MX36.1, MX37.1, MX38.1, MX39.1, MX40.1, MX41.1, MX42.1, MX43.1, MX44.1, MX45.1, MX46.1, U2.32
C4: MX47.1, MX48.1, MX49.1, MX50.1, MX51.1, MX52.1, MX53.1, MX54.1, MX55.1, MX56.1, U2.31
C5: MX57.1, MX58.1, MX59.1, MX60.1, MX61.1, MX62.1, MX63.1, MX64.1, MX65.1, MX66.1, U2.30
C6: MX67.1, MX68.1, MX69.1, MX70.1, MX71.1, MX72.1, MX73.1, MX74.1, MX75.1, MX76.1, MX77.1, MX78.1, MX79.1, MX80.2, MX81.2, U2.29
C7: MX82.1, MX83.1, MX84.1, MX85.1, MX86.1, MX87.1, U2.26
C8: MX88.1, MX89.1, MX90.1, MX91.1, MX92.1, MX93.1, MX94.1, MX95.1, MX96.1, U2.25
D+: R4.1, U2.4
D-: R5.1, U2.3
DG+: J1.3, R4.2
DG-: J1.2, R5.2
GND: C1.1, C2.2, C3.2, C4.1, C5.1, C6.2, C7.1, J1.4, R7.1, RGB1.3, RGB2.3, RGB3.3, RGB4.3, RGB5.3, RGB6.3, RGB7.3, RGB8.3, RGB9.3, RGB10.3, RGB11.3, RGB12.3, RGB13.3, RGB14.3, RGB15.3, RGB16.3, RGB17.3, RGB18.3, RGB19.3, RGB20.3, RGB21.3, RGB22.3, SW1.1, U1.1, U2.5, U2.15, U2.23, U2.35, U2.43, U2.45, Y1.2, Y1.4
MISO: D2.1, D14.1, D25.1, D35.1, D46.1, D56.1, D66.1, D76.1, D83.1, U1.6, U2.11
MOSI: D7.1, D19.1, D29.1, D39.1, D50.1, D60.1, D70.1, D78.1, D87.1, U1.4, U2.10
unnamed: C2.1, U2.17, Y1.1
unnamed: C3.1, U2.16, Y1.3
unnamed: C6.1, U2.6
unnamed: D1.2, MX1.2
unnamed: D2.2, MX2.2
unnamed: D3.2, MX3.2
unnamed: D4.2, MX4.2, MX8.1
unnamed: D5.2, MX5.2, MX6.2
unnamed: D6.2, MX7.2
unnamed: D7.2, MX9.2
unnamed: D8.2, MX10.2
unnamed: D9.2, MX11.2
unnamed: D10.2, MX12.2
unnamed: D11.2, MX13.2
unnamed: D12.2, MX14.2
unnamed: D13.2, MX15.2
unnamed: D14.2, MX16.2
unnamed: D15.2, MX17.2
unnamed: D16.2, MX18.2
unnamed: D17.2, MX19.2
unnamed: D18.2, MX20.2
unnamed: D19.2, MX21.2
unnamed: D20.2, MX22.2
unnamed: D21.2, MX23.2
unnamed: D22.2, MX24.2
unnamed: D23.2, MX25.2
unnamed: D24.2, MX26.2
unnamed: D25.2, MX27.2
unnamed: D26.2, MX28.2
unnamed: D27.2, MX29.2
unnamed: D28.2, MX30.2
unnamed: D29.2, MX31.2
unnamed: D30.2, MX32.2
unnamed: D31.2, MX33.2
unnamed: D32.2, MX34.2
unnamed: D33.2, MX35.2
unnamed: D34.2, MX36.2
unnamed: D35.2, MX37.2
unnamed: D36.2, MX38.2
unnamed: D37.2, MX39.2
unnamed: D38.2, MX40.2
unnamed: D39.2, MX41.2
unnamed: D40.2, MX42.2
unnamed: D41.2, MX43.2
unnamed: D42.2, MX44.2
unnamed: D43.2, MX45.2
unnamed: D44.2, MX46.2
unnamed: D45.2, MX47.2
unnamed: D46.2, MX48.2
unnamed: D47.2, MX49.2
unnamed: D48.2, MX50.2
unnamed: D49.2, MX51.2
unnamed: D50.2, MX52.2
unnamed: D51.2, MX53.2
unnamed: D52.2, MX54.2
unnamed: D53.2, MX55.2
unnamed: D54.2, MX56.2
unnamed: D55.2, MX57.2
unnamed: D56.2, MX58.2
unnamed: D57.2, MX59.2
unnamed: D58.2, MX60.2
unnamed: D59.2, MX61.2
unnamed: D60.2, MX62.2
unnamed: D61.2, MX63.2
unnamed: D62.2, MX64.2
unnamed: D63.2, MX65.2
unnamed: D64.2, MX66.2
unnamed: D65.2, MX67.2
unnamed: D66.2, MX68.2
unnamed: D67.2, MX69.2
unnamed: D68.2, MX70.2, MX71.2
unnamed: D69.2, MX72.2
unnamed: D70.2, MX73.2
unnamed: D71.2, MX74.2, MX75.2
unnamed: D72.2, MX76.2, MX80.1
unnamed: D73.2, MX77.2, MX81.1
unnamed: D74.2, MX78.2
unnamed: D75.2, MX79.2
unnamed: D76.2, MX82.2
unnamed: D77.2, MX83.2
unnamed: D78.2, MX84.2
unnamed: D79.2, MX85.2
unnamed: D80.2, MX86.2
unnamed: D81.2, MX87.2
unnamed: D82.2, MX88.2
unnamed: D83.2, MX89.2
unnamed: D84.2, MX90.2
unnamed: D85.2, MX91.2
unnamed: D86.2, MX92.2
unnamed: D87.2, MX93.2
unnamed: D88.2, MX94.2
unnamed: D89.2, MX95.2
unnamed: D90.2, MX96.2
unnamed: LED1.1, R2.1
unnamed: LED2.1, LED3.1, R3.1
unnamed: R1.1, RGB14.4
unnamed: R7.2, U2.33
unnamed: RGB1.4, RGB2.2
unnamed: RGB2.4, RGB3.2
unnamed: RGB3.4, RGB4.2
unnamed: RGB4.4, RGB5.2
unnamed: RGB5.4, RGB6.2
unnamed: RGB6.4, RGB7.2
unnamed: RGB7.4, RGB8.2
unnamed: RGB8.4, RGB9.2
unnamed: RGB9.4, RGB10.2
unnamed: RGB10.4, RGB11.2
unnamed: RGB11.4, RGB12.2
unnamed: RGB12.4, RGB13.2
unnamed: RGB13.4, RGB22.2
unnamed: RGB14.2, RGB15.4
unnamed: RGB15.2, RGB16.4
unnamed: RGB16.2, RGB17.4
unnamed: RGB17.2, RGB18.4
unnamed: RGB18.2, RGB19.4
unnamed: RGB19.2, RGB20.4
unnamed: RGB20.2, RGB21.4
unnamed: RGB21.2, RGB22.4
R0: D1.1, D13.1, D24.1, D34.1, D45.1, D55.1, D65.1, D82.1, U1.2, U2.9
R3: D8.1, D20.1, D30.1, D40.1, D51.1, D61.1, D71.1, D79.1, D88.1, U2.12
R4: D3.1, D15.1, D26.1, D36.1, D47.1, D57.1, D67.1, D84.1, U2.18
R5: D9.1, D21.1, D31.1, D41.1, D52.1, D62.1, D72.1, D80.1, D89.1, U2.19
R6: D4.1, D16.1, D27.1, D37.1, D48.1, D58.1, U2.40
R7: D10.1, D22.1, D32.1, D42.1, D53.1, D63.1, D73.1, U2.41
R8: D5.1, D17.1, D28.1, D38.1, D49.1, D59.1, D68.1, D85.1, U2.27
R9: D11.1, D23.1, D33.1, D43.1, D54.1, D64.1, D74.1, U2.28
R10: D6.1, D18.1, D69.1, D77.1, D86.1, U2.22
R11: D12.1, D44.1, D75.1, D81.1, D90.1, U2.21
RGB: R1.2, U2.20
RST: R6.2, SW1.2, U1.3, U2.13
indicator1: R2.2, U2.8
indicator2: R3.2, U2.38
